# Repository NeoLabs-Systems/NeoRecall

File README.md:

<h1 align="center">NeoRecall</h1>

<p align="center"><strong>Private audio memory you host yourself.</strong></p>

Browser and coarse server analytics are enabled by default and can be disabled; see [analytics](docs/docs/analytics.md).

<p align="center">
  Records your day anywhere, turns every conversation into a searchable memory,<br>
  and answers from it. On your hardware, with the models you choose.
</p>

<p align="center">

</p>

<p align="center">

</p>

<p align="center">
  
</p>

https://github.com/user-attachments/assets/eb40bc78-905b-459a-bdea-a49aba3c9c09

<table>
  <tr>
    <td width="33%" valign="top">
      <h3>🏠 On your hardware</h3>
      Your server, your database, your search index.<br>
      Desktop app, Docker or one script.
    </td>
    <td width="33%" valign="top">
      <h3>🔐 Yours</h3>
      Open source under AGPL-3.0.<br>
      Any transcription and language model, local ones included.
    </td>
    <td width="33%" valign="top">
      <h3>🧾 Proof before delete</h3>
      Audio is removed only after the transcript is durable.
    </td>
  </tr>
</table>

---

## 🚀 Install

| | | |
| --- | --- | --- |
| 🖥️ **Desktop app** | macOS 13+ and Windows 10/11. **Set up NeoRecall on this computer** installs the server for you, no terminal. | [Download](https://github.com/NeoLabs-Systems/NeoRecall/releases/latest) |
| 🐳 **Docker** | Home servers, NAS boxes and VPS. | [Guide](docs/docs/installation.md#docker-compose) |
| 📜 **Script** | Linux or macOS with Git and Node.js 20+. | [Guide](docs/docs/installation.md) |

**Script**

```bash
bash <(curl -fsSL https://raw.githubusercontent.com/NeoLabs-Systems/NeoRecall/main/install.sh)
```

Then open **http://localhost:4500** once `neorecall status` reports a running service. The first account you create becomes the administrator; the app then asks for your transcription and language-model services (or an on-host model) and tests both.

## ✨ What it does

<table>
  <tr>
    <td width="33%" valign="top"><b>🎙️ Records anywhere</b><br>Browser, macOS and Windows with microphone and system audio. Quick capture sits in your tray.</td>
    <td width="33%" valign="top"><b>🧠 Memories, not transcripts</b><br>Each conversation becomes one memory with people, promises, decisions and tasks, written when it ends.</td>
    <td width="33%" valign="top"><b>💬 Ask your day</b><br>"What did I agree to this morning?" Answers cite the moments they came from.</td>
  </tr>
  <tr>
    <td valign="top"><b>🗣️ Knows who said what</b><br>Speech and voices are detected on your machine (31 MB of models). The same voice is recognized weeks later.</td>
    <td valign="top"><b>♾️ Never stops</b><br>Upload, transcription and conversation detection run during capture. Long recordings are read in windows and folded into one memory.</td>
    <td valign="top"><b>📴 Offline first</b><br>Clients buffer decodable chunks and resume idempotent uploads when the server is back.</td>
  </tr>
  <tr>
    <td valign="top"><b>📟 Wearables and devices</b><br>Omi, Plaud, Memoket and more over Bluetooth, plus NeoRecall Desk, a Raspberry Pi call recorder.</td>
    <td valign="top"><b>🎧 Meetings and voice</b><br>Zoom, Teams, Webex and FaceTime detection, and a Discord notetaker bot you run yourself.</td>
    <td valign="top"><b>🔌 NeoAgent and MCP</b><br>Connect <a href="https://github.com/NeoLabs-Systems/NeoAgent">NeoAgent</a>, or paste the MCP URL into Claude, ChatGPT or Cursor for read-only recall.</td>
  </tr>
  <tr>
    <td valign="top"><b>📝 Context</b><br>Add highlights, notes, photos and files while recording. They attach to the right memory.</td>
    <td valign="top"><b>🛡️ Consent built in</b><br>A recording notice and a persistent recording state. There is no covert mode.</td>
    <td valign="top"><b>👥 Multi-user</b><br>Per-account memory, admin role, two-factor and security keys, encrypted backups.</td>
  </tr>
</table>

**Inference:** bring any OpenAI-compatible transcription and language-model service, or run Whistle (speech to text) and Gemma 2 2B (memories and Ask) on the server itself. NeoRecall bundles no model you did not choose.

## 🧭 Explore it

| 🕒 Moments | 🧠 Memories |
| --- | --- |
|  |  |
| **💬 Ask** | **🔎 One memory** |
|  |  |

## 📚 Docs

| Start | Use | Run |
| --- | --- | --- |
| [Installation](docs/docs/installation.md) | [Recording](docs/docs/recording.md) | [Configuration](docs/docs/configuration.md) |
| [Privacy and consent](docs/docs/privacy-and-consent.md) | [NeoRecall Desk](docs/docs/desk-appliance.md) | [Troubleshooting](docs/docs/troubleshooting.md) |
| [Architecture](docs/docs/architecture.md) | [Contributing](CONTRIBUTING.md) | [Security](SECURITY.md) |

Full docs: **[neolabs-systems.github.io/NeoRecall/docs](https://neolabs-systems.github.io/NeoRecall/docs/)**

## 🧪 Project status

- **Beta.** Maintained mainly by one person. Expect breaking changes.
- **Privacy.** Read [privacy and consent](docs/docs/privacy-and-consent.md) and get the consent your jurisdiction requires before recording anyone else.
- **Help.** [Discussions](https://github.com/NeoLabs-Systems/NeoRecall/discussions) for questions, [Issues](https://github.com/NeoLabs-Systems/NeoRecall/issues) for bugs, [SECURITY.md](SECURITY.md) for vulnerabilities.

## 📄 License

[AGPL-3.0-only](LICENSE).

<p align="center"><sub>Made with ❤️ by <a href="https://github.com/neooriginal">Neo</a> · <a href="https://github.com/NeoLabs-Systems">NeoLabs Systems</a></sub></p>

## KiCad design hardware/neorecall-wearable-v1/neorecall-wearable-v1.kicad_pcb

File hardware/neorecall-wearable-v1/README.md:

# NeoRecall Wearable v1 hardware

This directory contains the concrete KiCad 10 schematic, PCB layout, and reviewed component set for a 28 mm × 38 mm NeoRecall recorder. It is a four-layer, 0.8 mm design with two TDK T5848 I²S microphones, Wi-Fi 6/BLE 5.3, removable 16 GB storage, protected three-wire LiPo support with a 10 kΩ pack thermistor, USB-C charging/flashing, and a center user/boot/wake button.

## What is complete

- Native KiCad schematic with exact part numbers, footprints, pin mapping, net names, and manufacturing notes.
- USB-C 5 V input, ESD protection, native ESP32-C6 USB, BQ24074 power-path charging, and a TPS63021 3.3 V buck-boost supply.
- Two independently selectable T5848 microphones on one stereo I²S bus at 1.85 V.
- SPI microSD with card detection, series damping, pull resistors, and local bulk capacitance.
- Visible recording and charging indicators, battery measurement, five zero-height UART/power/test pads, and monitored charger/regulator status.
- Manufacturer-drawing-derived footprints for the ESP32-C6-MINI-1, T5848, TPS63021 DSJ package, XFL4020 inductor, MEM2085 socket, and Molex USB-C socket.
- Machine-readable BOM, complete pin-to-net matrix, and electrical invariant checks.
- Four-layer fully connected PCB, locked symmetric ENIG stackup, all-layer antenna keepout, uninterrupted In1 GND plane, In2 3V3 distribution plane, and real KiCad 3D renders.
- Hardware power gates for both the microphone domain and microSD domain, with pull-downs that default both domains off during reset/deep sleep.
- Internal rear-side microSD socket whose complete body/card envelope stays inside the PCB outline.
- Hardware-bound recording indicator: powering the microphone domain necessarily lights the red LED.

The board is a **Rev C production candidate**, not production-qualified hardware. ERC, schematic parity, opens, shorts, ordinary copper clearance, and track-crossing checks are zero. The remaining nine DRC markers are the exact reviewed acoustic-port and connector-edge constructions in `DRC_WAIVERS.md`. The BQ_TS escape was narrowed locally to 0.10 mm and now retains at least 0.20 mm routed-edge clearance for JLCPCB. The package is for EVT/DFM, not unattended volume release.

## Files

- `neorecall-wearable-v1.kicad_sch` — generated KiCad schematic.
- `neorecall-wearable-v1.kicad_pro` — KiCad project.
- `neorecall-wearable-v1.kicad_pcb` — actual four-layer PCB layout.
- `renders/neorecall-top.png`, `renders/neorecall-bottom.png`, and `renders/neorecall-usb.png` — KiCad board and connector renders.
- `../../output/pdf/neorecall-wearable-v1-schematic.pdf` — rendered one-page A2 schematic PDF.
- `bom.csv` — one row per populated component with manufacturer part numbers.
- `pin-net-matrix.csv` — auditable pin-level connectivity.
- `design-summary.json` — dimensions and power/storage configuration.
- `PLACEMENT.md` — concrete PCB placement and thickness plan.
- `ASSEMBLY.md` — hand-assembly, bring-up, and battery-safety procedure.
- `SOURCES.md` — primary manufacturer sources used for electrical and mechanical decisions.
- `tools/generate_schematic.py` — electrical source of truth and deterministic generator.
- `tools/verify_design.py` — offline structural and electrical verification.
- `tools/verify_release.py` — verifies ERC/DRC reports and the exact mechanical-waiver signature.
- `tools/verify_functional_margins.py` — independently rechecks critical pin paths, charger/ADC/audio/storage arithmetic, and the complete JLC ZIP without importing the generator.
- `tools/verify_layout.py` — verifies board geometry, planes, antenna keepout, internal card envelope, switch nodes, power widths, and USB routing metrics with pcbnew.
- `tools/export_jlcpcb.sh` — generates the conventional four-layer Gerber/drill ZIP for direct JLCPCB upload.
- `firmware/manufacturing-test/` — build-tested ESP-IDF first-article firmware for power status, battery ADC, stereo microphones, microSD write/read/isolation, button, and deep-sleep wake.
- `fabrication/` — current EVT Gerber/drill/placement package and fab notes.
- `ELECTRICAL_AUDIT.md` — calculations, fault scenarios, sourcing review, and physical qualification matrix.

## Generate and verify

The only Python dependency is small; no KiCad application or model download is needed to regenerate the schematic.

```bash
python3 -m venv .venv-hardware
.venv-hardware/bin/pip install -r hardware/neorecall-wearable-v1/tools/requirements.txt
.venv-hardware/bin/python hardware/neorecall-wearable-v1/tools/generate_schematic.py
# Run sync_board.py with KiCad 10's bundled Python/pcbnew after regenerating.
.venv-hardware/bin/python hardware/neorecall-wearable-v1/tools/verify_design.py
.venv-hardware/bin/python hardware/neorecall-wearable-v1/tools/verify_release.py
.venv-hardware/bin/python hardware/neorecall-wearable-v1/tools/verify_functional_margins.py
# Run verify_layout.py with KiCad's bundled Python/pcbnew environment.
```

Open `hardware/neorecall-wearable-v1/neorecall-wearable-v1.kicad_pro` in KiCad 10 or newer. Run ERC and DRC again after any hand edit. Before ordering a PCB, select the actual 0.8 mm board-house stackup, solve USB D+/D− for 90 Ω differential impedance, and compare 1:1 footprint prints against physical parts.

The assembly BOM is now 71 fitted parts. TP1–TP5 are bare ENIG pogo/solder pads, excluded from the BOM and pick-and-place data: GPIO16/UART TX, GPIO17/UART RX, ESP_EN, 3V3, and GND. GPIO16/17 can be reassigned by firmware after boot, providing a compact two-signal expansion/debug interface without a connector, board-area increase, or assembly height.

## Fixed electrical decisions

- MCU/radio: `ESP32-C6-MINI-1-H8`, integrated antenna and 8 MB flash.
- Storage: `MEM2085-00-115-00-A` low-profile microSD socket with a genuine 16 GB high-endurance card.
- Microphones: two `MMICT5848-00-012`, one LR pin low and one high.
- Charger: `BQ24074RGTR`, approximately 201 mA cell charge, 500 mA USB input mode, power-path enabled.
- Main supply: fixed 3.3 V `TPS63021DSJR` with `XFL4020-152MEC` and 66 µF nominal output capacitance.
- Microphone supply: switchable 1.85 V `TPS7A20185PDBVR` plus `TXU0304PWR` level translation.
- Storage supply: switchable 3.3 V `TPS22918DBVR` with a 1 nF CT capacitor for an approximately 1.68 ms rail rise; firmware must unmount the card, disable SPI pins, then drive `SD_POWER_EN` low before deep sleep.
- Battery: protected 1S LiPo only, keyed three-pole JST-SH: pin 1 BAT+, pin 2 pack 10 kΩ NTC to GND at 25 °C, pin 3 GND.

The pack thermistor gives the BQ24074 real charge-temperature qualification. It is not a substitute for a protected, reputable cell, a locked mating-cable pinout, or enclosure thermal validation.

## Deep-sleep design

- `MIC_POWER_EN` removes the microphone LDO/translator domain; `R31` keeps it off through reset.
- `SD_POWER_EN` removes microSD and all card pull-up current; `R32` keeps it off through reset.
- TPS63021 power-save mode remains enabled so the always-on 3.3 V rail is efficient at light load.
- The battery divider is 1 MΩ + 330 kΩ, approximately 3.2 µA at a full 4.2 V cell.
- The center button reaches both GPIO0 (deep-sleep-capable wake) and GPIO9 (ROM boot strap); firmware must configure both as inputs and use GPIO0 for deep-sleep wake. There is intentionally no covert always-recording mode.

The estimated board-level deep-sleep budget is a design estimate, not a guaranteed measurement. Regulator, charger, MCU, divider, load-switch, translator, card leakage, temperature, and assembly contamination must be measured on at least three assembled boards before an endurance claim is published.

## Size and sourcing decision

The active outline remains 28 mm × 38 mm. The RF module antenna keepout, internal microSD envelope, opposed microphone ports, and edge-mounted USB and battery connectors set the usable geometry; shrinking the center PTS810 switch does not reduce the outline. Replacing it with a less common, less hand-reworkable switch would trade usability and sourcing resilience for no board-size win. The retained active ICs are current manufacturer parts, while the five incorrectly BOM-listed test-point components have been removed. The 1.85 V microphone rail and level translator remain electrically necessary because T5848 operates from 1.62–1.98 V; the obsolete 3.3 V ICS-43434 is not a valid consolidation substitute.

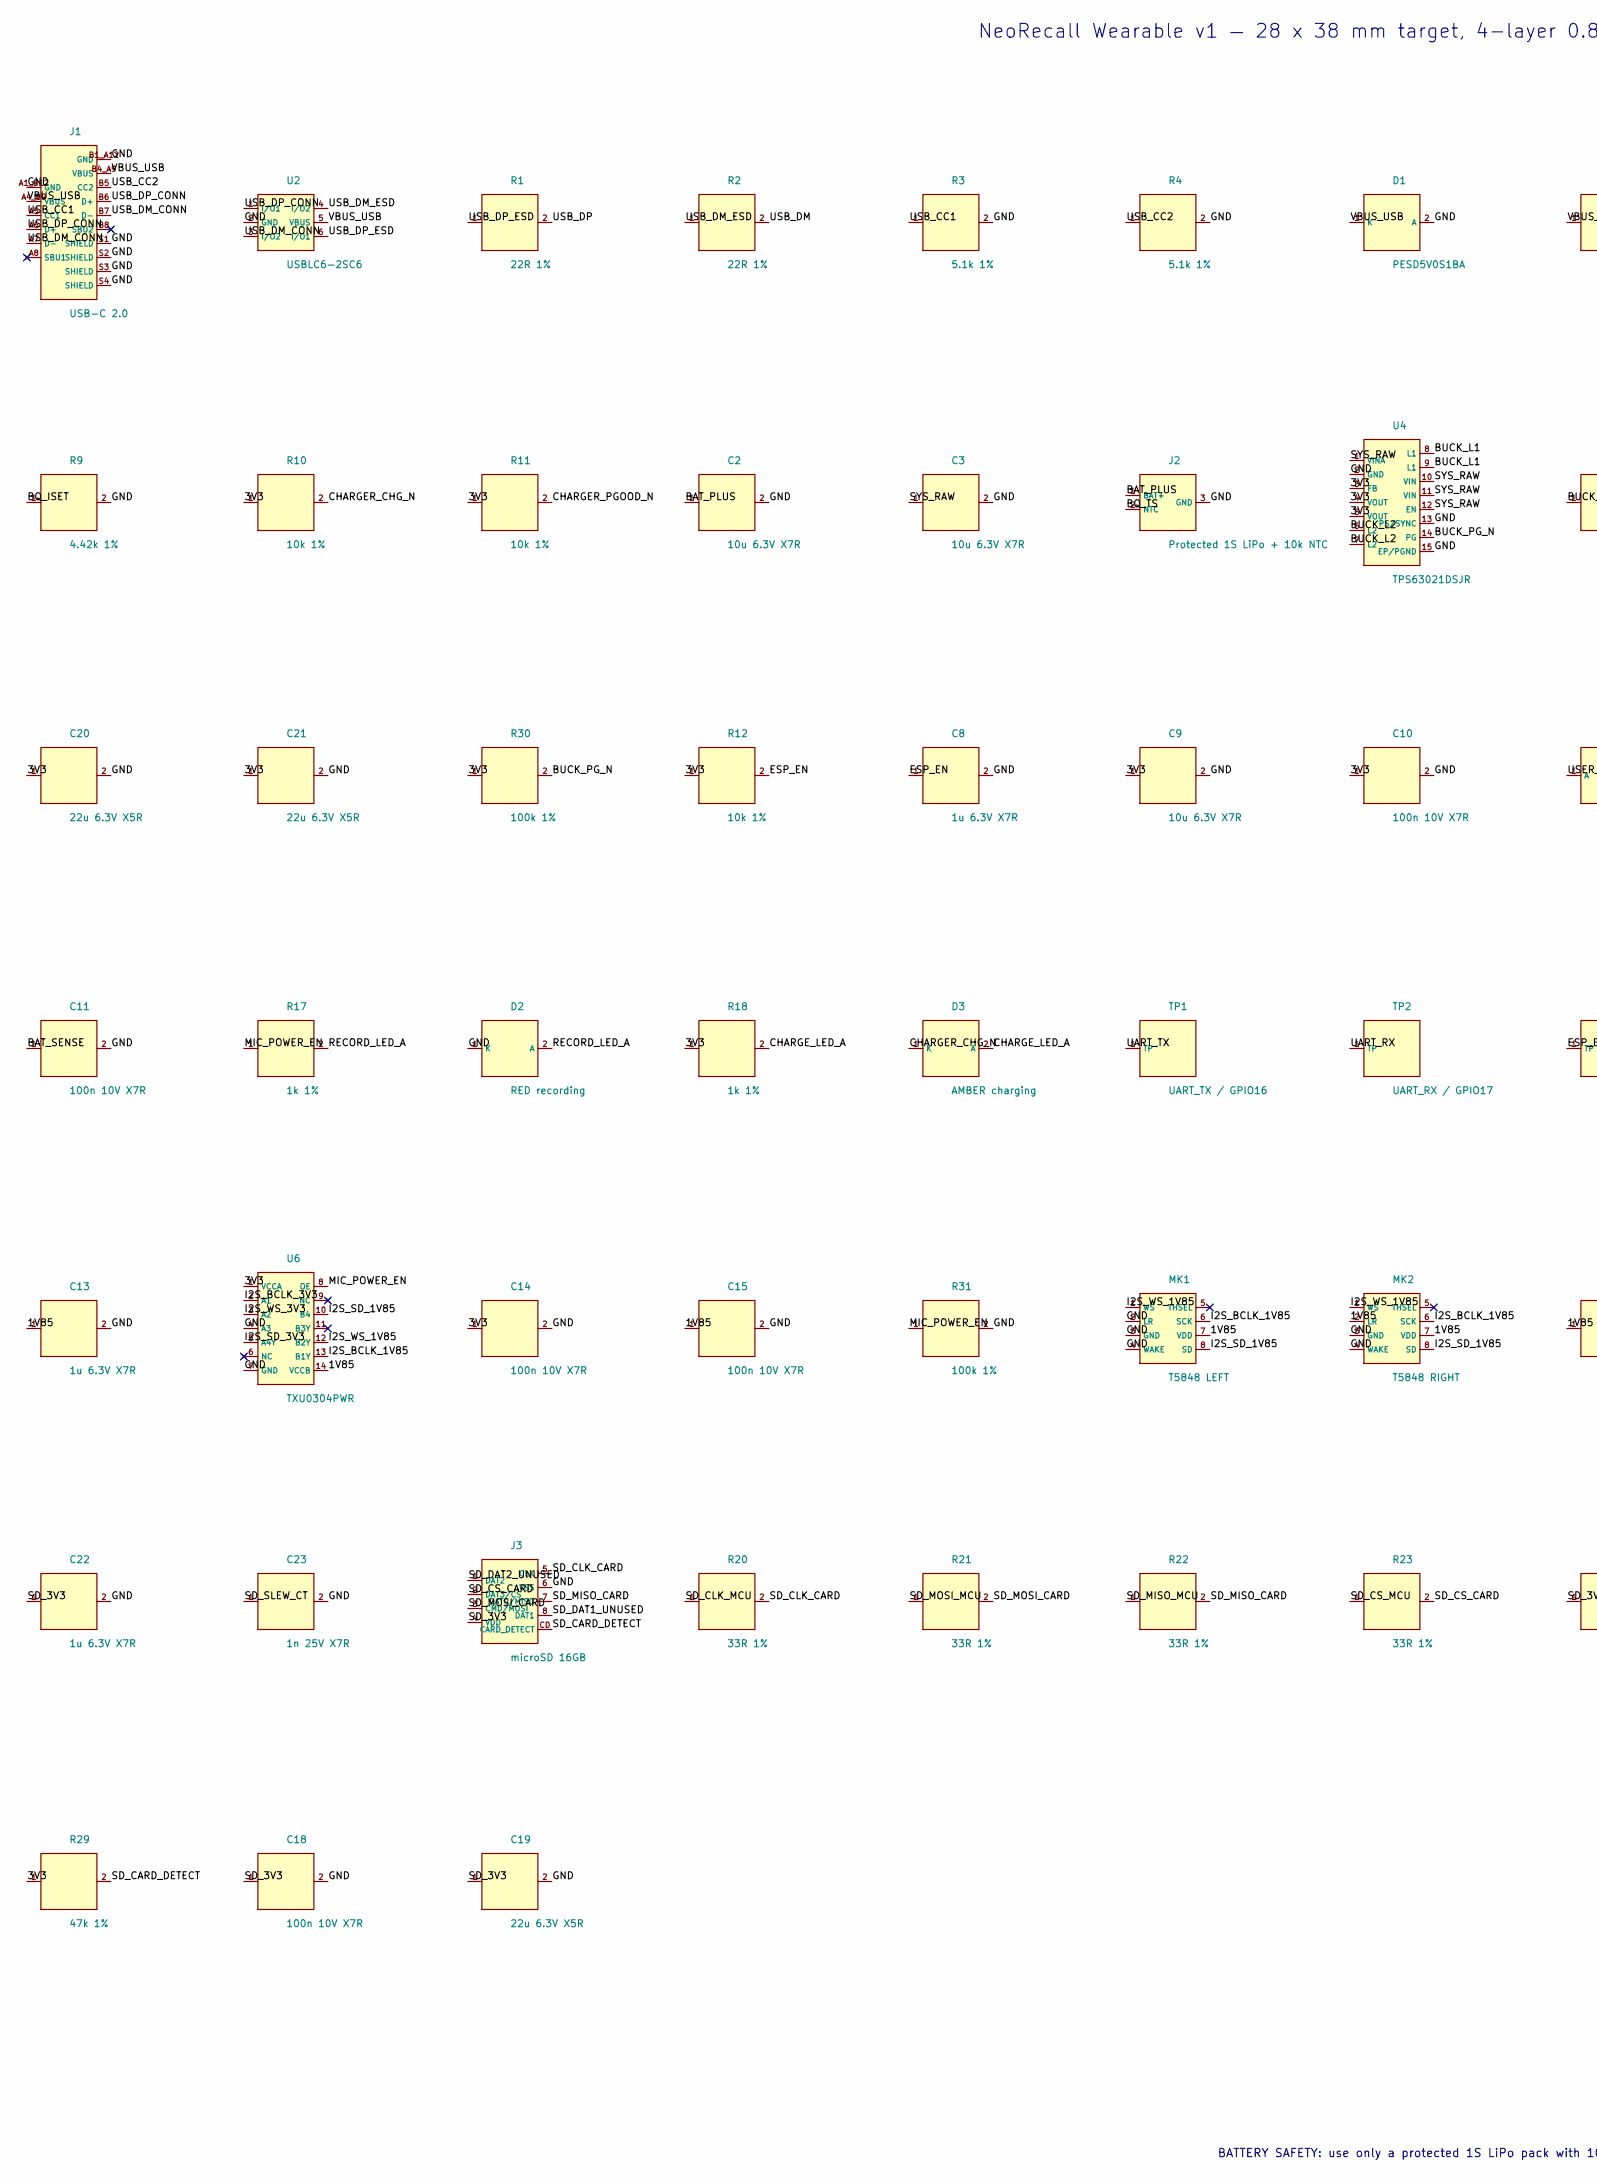
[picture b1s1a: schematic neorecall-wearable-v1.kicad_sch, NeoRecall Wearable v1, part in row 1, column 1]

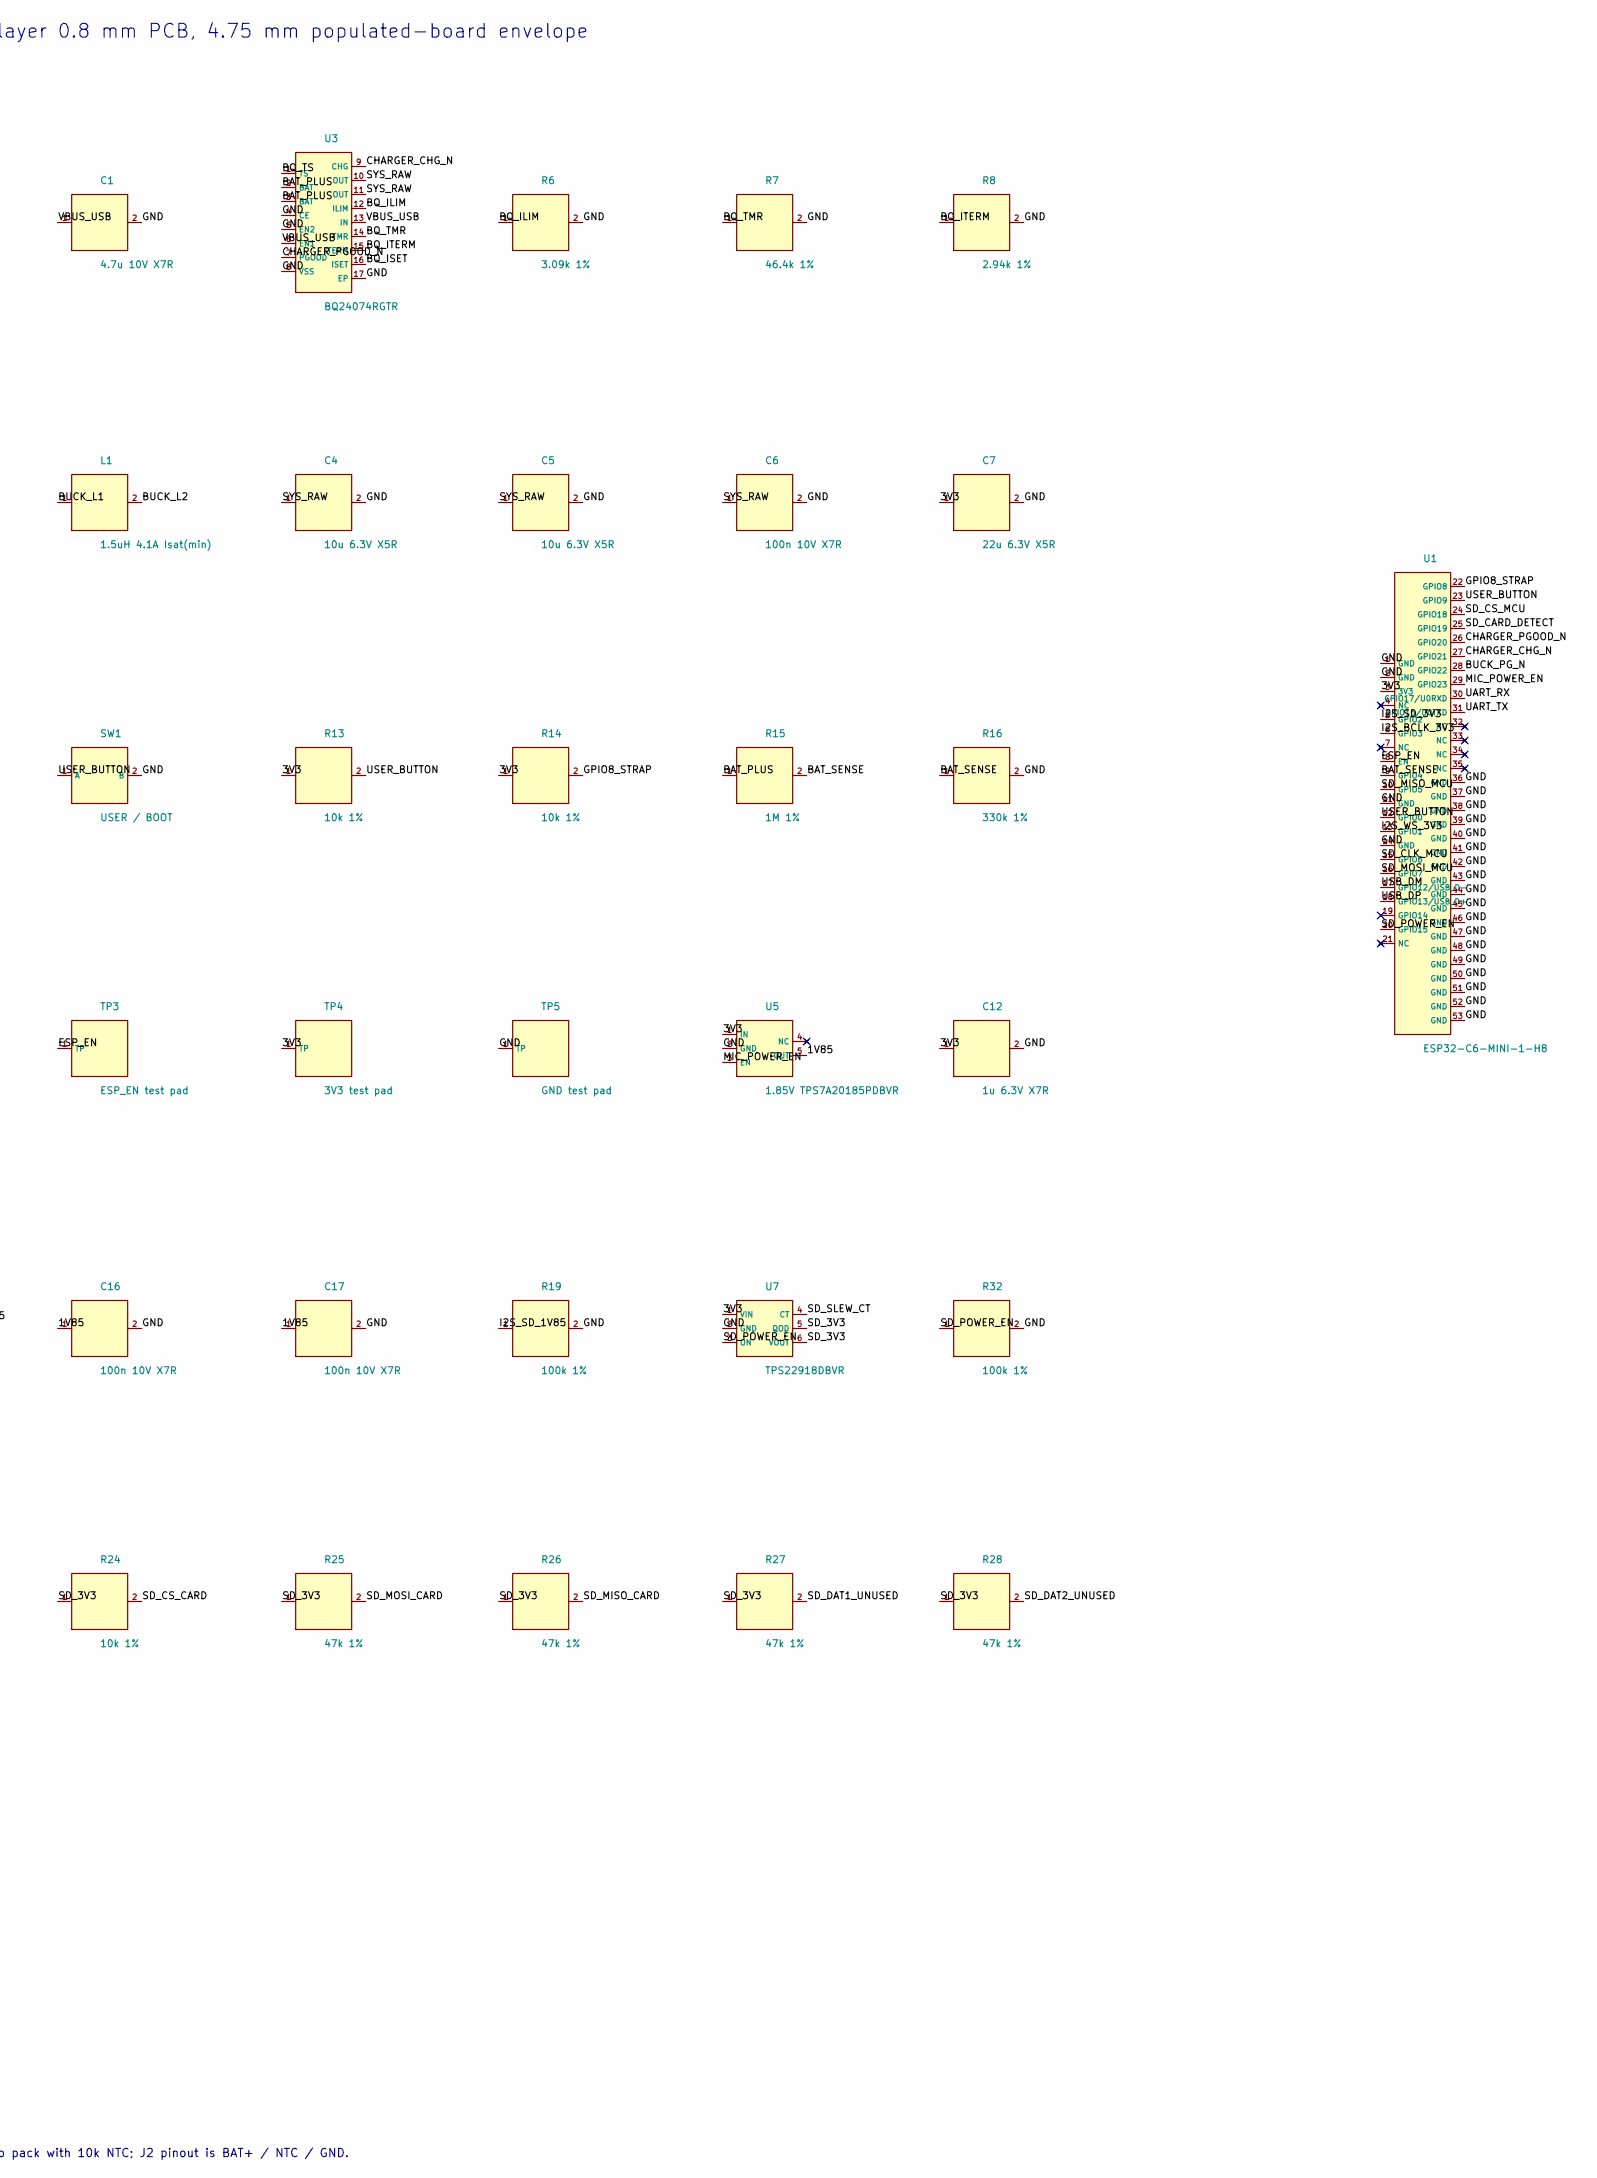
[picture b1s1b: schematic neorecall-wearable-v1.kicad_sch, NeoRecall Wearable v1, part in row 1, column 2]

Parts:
C1: 4.7u 10V X7R; C_0603_1608Metric
C2, C3, C9: 10u 6.3V X7R; C_0603_1608Metric
C4, C5: 10u 6.3V X5R; C_0603_1608Metric
C6, C10, C11, C14, C15, C16, C17, C18: 100n 10V X7R; C_0603_1608Metric
C7, C19, C20, C21: 22u 6.3V X5R; C_0805_2012Metric
C8, C12, C13, C22: 1u 6.3V X7R; C_0603_1608Metric
C23: 1n 25V X7R; C_0402_1005Metric
D1: PESD5V0S1BA; D_SOD-323
D2: RED recording; LED_0603_1608Metric
D3: AMBER charging; LED_0603_1608Metric
J1: USB-C 2.0; Molex_2169900003
J2: Protected 1S LiPo + 10k NTC; JST_SH_SM03B-SRSS-TB_1x03-1MP_P1.00mm_Horizontal
J3: microSD 16GB; GCT_MEM2085
L1: 1.5uH 4.1A Isat(min); Coilcraft_XFL4020
MK1: T5848 LEFT; T5848_LGA8_BottomPort
MK2: T5848 RIGHT; T5848_LGA8_BottomPort
R1, R2: 22R 1%; R_0402_1005Metric
R3, R4: 5.1k 1%; R_0603_1608Metric
R6: 3.09k 1%; R_0603_1608Metric
R7: 46.4k 1%; R_0603_1608Metric
R8: 2.94k 1%; R_0603_1608Metric
R9: 4.42k 1%; R_0603_1608Metric
R10, R11, R12, R13, R14, R24: 10k 1%; R_0603_1608Metric
R15: 1M 1%; R_0603_1608Metric
R16: 330k 1%; R_0603_1608Metric
R17, R18: 1k 1%; R_0603_1608Metric
R19, R30, R31, R32: 100k 1%; R_0603_1608Metric
R20, R21, R22, R23: 33R 1%; R_0603_1608Metric
R25, R26, R27, R29: 47k 1%; R_0603_1608Metric
R28: 47k 1%; R_0402_1005Metric
SW1: USER / BOOT; SW_SPST_PTS810
TP1: UART_TX / GPIO16; TestPoint_Pad_D1.0mm
TP2: UART_RX / GPIO17; TestPoint_Pad_D1.0mm
TP3: ESP_EN test pad; TestPoint_Pad_D1.0mm
TP4: 3V3 test pad; TestPoint_Pad_D1.0mm
TP5: GND test pad; TestPoint_Pad_D1.0mm
U1: ESP32-C6-MINI-1-H8; ESP32-C6-MINI-1
U2: USBLC6-2SC6; SOT-23-6
U3: BQ24074RGTR; VQFN-16-1EP_3x3mm_P0.5mm_EP1.45x1.45mm
U4: TPS63021DSJR; TI_DSJ_VSON14_3x4mm
U5: 1.85V TPS7A20185PDBVR; SOT-23-5
U6: TXU0304PWR; TSSOP-14_4.4x5mm_P0.65mm
U7: TPS22918DBVR; SOT-23-6

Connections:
/1V85: C13.1, C15.1, C16.1, C17.1, MK1.7 (VDD), MK2.2 (LR), MK2.7 (VDD), U5.5 (OUT), U6.14 (VCCB)
/3V3: C7.1, C9.1, C10.1, C12.1, C14.1, C20.1, C21.1, R10.1, R11.1, R12.1, R13.1, R14.1, R18.1, R29.1, R30.1, TP4.1, U1.3 (3V3), U4.3 (FB), U4.4 (VOUT), U4.5 (VOUT), U5.1 (IN), U6.1 (VCCA), U7.1 (VIN)
/BAT_PLUS: C2.1, J2.1 (BAT+), R15.1, U3.2 (BAT), U3.3 (BAT)
/BAT_SENSE: C11.1, R15.2, R16.1, U1.9 (GPIO4)
/BQ_ILIM: R6.1, U3.12 (ILIM)
/BQ_ISET: R9.1, U3.16 (ISET)
/BQ_ITERM: R8.1, U3.15 (ITERM)
/BQ_TMR: R7.1, U3.14 (TMR)
/BQ_TS: J2.2 (NTC), U3.1 (TS)
/BUCK_L1: L1.1, U4.8 (L1), U4.9 (L1)
/BUCK_L2: L1.2, U4.6 (L2), U4.7 (L2)
/BUCK_PG_N: R30.2, U1.28 (GPIO22), U4.14 (PG)
/CHARGER_CHG_N: D3.1 (K), R10.2, U1.27 (GPIO21), U3.9 (CHG)
/CHARGER_PGOOD_N: R11.2, U1.26 (GPIO20), U3.7 (PGOOD)
/CHARGE_LED_A: D3.2 (A), R18.2
/ESP_EN: C8.1, R12.2, TP3.1, U1.8 (EN)
/GND: C1.2, C2.2, C3.2, C4.2, C5.2, C6.2, C7.2, C8.2, C9.2, C10.2, C11.2, C12.2, C13.2, C14.2, C15.2, C16.2, C17.2, C18.2, C19.2, C20.2, C21.2, C22.2, C23.2, D1.2 (A), D2.1 (K), J1.A1_B12 (GND), J1.B1_A12 (GND), J1.S1 (SHIELD), J1.S2 (SHIELD), J1.S3 (SHIELD), J1.S4 (SHIELD), J2.3 (GND), J3.6 (VSS), MK1.2 (LR), MK1.3 (GND), MK1.4 (WAKE), MK2.3 (GND), MK2.4 (WAKE), R3.2, R4.2, R6.2, R7.2, R8.2, R9.2, R16.2, R19.2, R31.2, R32.2, SW1.2 (B), TP5.1, U1.1 (GND), U1.2 (GND), U1.11 (GND), U1.14 (GND), U1.36 (GND), U1.37 (GND), U1.38 (GND), U1.39 (GND), U1.40 (GND), U1.41 (GND), U1.42 (GND), U1.43 (GND), U1.44 (GND), U1.45 (GND), U1.46 (GND), U1.47 (GND), U1.48 (GND), U1.49 (GND), U1.50 (GND), U1.51 (GND), U1.52 (GND), U1.53 (GND), U2.2 (GND), U3.4 (CE), U3.5 (EN2), U3.8 (VSS), U3.17 (EP), U4.2 (GND), U4.13 (PS/SYNC), U4.15 (EP/PGND), U5.2 (GND), U6.4 (A3), U6.7 (GND), U7.2 (GND)
/GPIO8_STRAP: R14.2, U1.22 (GPIO8)
/I2S_BCLK_1V85: MK1.6 (SCK), MK2.6 (SCK), U6.13 (B1Y)
/I2S_BCLK_3V3: U1.6 (GPIO3), U6.2 (A1)
/I2S_SD_1V85: MK1.8 (SD), MK2.8 (SD), R19.1, U6.10 (B4)
/I2S_SD_3V3: U1.5 (GPIO2), U6.5 (A4Y)
/I2S_WS_1V85: MK1.1 (WS), MK2.1 (WS), U6.12 (B2Y)
/I2S_WS_3V3: U1.13 (GPIO1), U6.3 (A2)
/MIC_POWER_EN: R17.1, R31.1, U1.29 (GPIO23), U5.3 (EN), U6.8 (OE)
/RECORD_LED_A: D2.2 (A), R17.2
/SD_3V3: C18.1, C19.1, C22.1, J3.4 (VDD), R24.1, R25.1, R26.1, R27.1, R28.1, U7.5 (QOD), U7.6 (VOUT)
/SD_CARD_DETECT: J3.CD (CARD_DETECT), R29.2, U1.25 (GPIO19)
/SD_CLK_CARD: J3.5 (CLK), R20.2
/SD_CLK_MCU: R20.1, U1.15 (GPIO6)
/SD_CS_CARD: J3.2 (DAT3/CS), R23.2, R24.2
/SD_CS_MCU: R23.1, U1.24 (GPIO18)
/SD_DAT1_UNUSED: J3.8 (DAT1), R27.2
/SD_DAT2_UNUSED: J3.1 (DAT2), R28.2
/SD_MISO_CARD: J3.7 (DAT0/MISO), R22.2, R26.2
/SD_MISO_MCU: R22.1, U1.10 (GPIO5)
/SD_MOSI_CARD: J3.3 (CMD/MOSI), R21.2, R25.2
/SD_MOSI_MCU: R21.1, U1.16 (GPIO7)
/SD_POWER_EN: R32.1, U1.20 (GPIO15), U7.3 (ON)
/SD_SLEW_CT: C23.1, U7.4 (CT)
/SYS_RAW: C3.1, C4.1, C5.1, C6.1, U3.10 (OUT), U3.11 (OUT), U4.1 (VINA), U4.10 (VIN), U4.11 (VIN), U4.12 (EN)
/UART_RX: TP2.1, U1.30 (GPIO17/U0RXD)
/UART_TX: TP1.1, U1.31 (GPIO16/U0TXD)
/USB_CC1: J1.A5 (CC1), R3.1
/USB_CC2: J1.B5 (CC2), R4.1
/USB_DM: R2.2, U1.17 (GPIO12/USB_D-)
/USB_DM_CONN: J1.A7 (D-), J1.B7 (D-), U2.3 (I/O2)
/USB_DM_ESD: R2.1, U2.4 (I/O2)
/USB_DP: R1.2, U1.18 (GPIO13/USB_D+)
/USB_DP_CONN: J1.A6 (D+), J1.B6 (D+), U2.1 (I/O1)
/USB_DP_ESD: R1.1, U2.6 (I/O1)
/USER_BUTTON: R13.2, SW1.1 (A), U1.12 (GPIO0), U1.23 (GPIO9)
/VBUS_USB: C1.1, D1.1 (K), J1.A4_B9 (VBUS), J1.B4_A9 (VBUS), U2.5 (VBUS), U3.6 (EN1), U3.13 (IN)

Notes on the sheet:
NeoRecall Wearable v1 — 28 x 38 mm target, 4-layer 0.8 mm PCB, 4.75 mm populated-board envelope
BATTERY SAFETY: use only a protected 1S LiPo pack with 10k NTC; J2 pinout is BAT+ / NTC / GND.

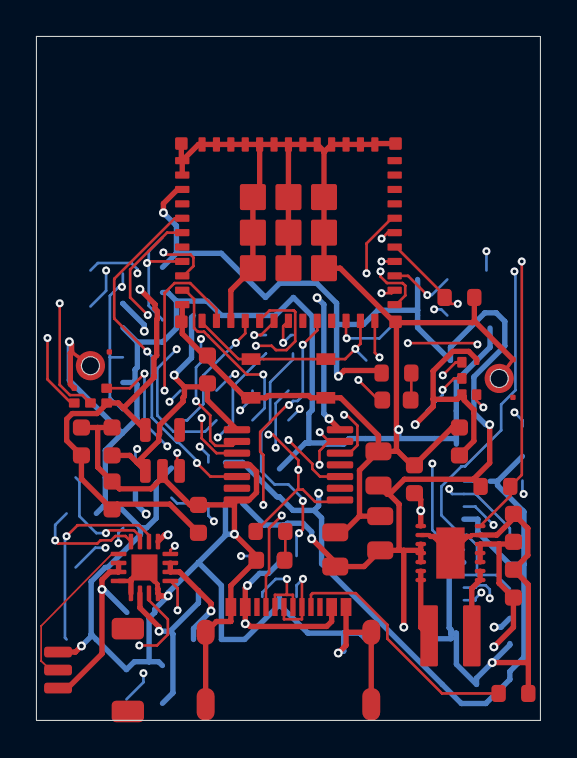
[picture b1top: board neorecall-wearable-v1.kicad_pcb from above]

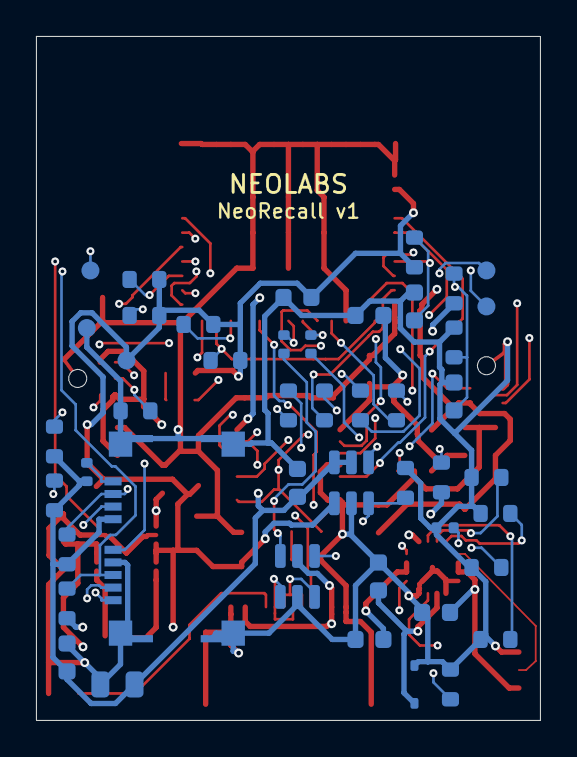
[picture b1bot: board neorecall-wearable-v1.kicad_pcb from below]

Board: 4 copper layers, 28.0 x 38.0 mm, 76 parts (46 on the bottom side), 53 nets.

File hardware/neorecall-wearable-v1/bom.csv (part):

Reference,Quantity,Value,Manufacturer,MPN,Footprint,Datasheet,Assembly note
J1,1,USB-C 2.0,Molex,216990-0003,NeoRecall_Wearable:Molex_2169900003,https://www.molex.com/en-us/products/part-detail/2169900003,Mid-mount; intended for 0.8 mm PCB
U2,1,USBLC6-2SC6,STMicroelectronics,USBLC6-2SC6,Package_TO_SOT_SMD:SOT-23-6,https://www.st.com/resource/en/datasheet/usblc6-2.pdf,
R1,1,22R 1%,Yageo,RC0402FR-0722RL,Resistor_SMD:R_0402_1005Metric,https://www.yageo.com/en/ProductSearch/PartDetail?partNo=RC0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,Place immediately at the ESP32 USB D+ pin; 0402 permits matched side-by-side breakout
R2,1,22R 1%,Yageo,RC0402FR-0722RL,Resistor_SMD:R_0402_1005Metric,https://www.yageo.com/en/ProductSearch/PartDetail?partNo=RC0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,Place immediately at the ESP32 USB D- pin; 0402 permits matched side-by-side breakout
R3,1,5.1k 1%,Yageo,RC0603FR-075K1L,Resistor_SMD:R_0603_1608Metric,https://www.yageo.com/,
R4,1,5.1k 1%,Yageo,RC0603FR-075K1L,Resistor_SMD:R_0603_1608Metric,https://www.yageo.com/,
D1,1,PESD5V0S1BA,Nexperia,"PESD5V0S1BA,115",Diode_SMD:D_SOD-323,https://assets.nexperia.com/documents/data-sheet/PESD5V0S1BA.pdf,
C1,1,4.7u 10V X7R,Murata,GRM188Z71A475KE15D,Capacitor_SMD:C_0603_1608Metric,https://www.murata.com/en-us/products/productdetail?partno=G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,
U3,1,BQ24074RGTR,Texas Instruments,BQ24074RGTR,Package_DFN_QFN:VQFN-16-1EP_3x3mm_P0.5mm_EP1.45x1.45mm,https://www.ti.com/lit/ds/symlink/bq24074.pdf,"201 mA charge, 20 mA termination, USB500 input mode"
R6,1,3.09k 1%,Yageo,RC0603FR-073K09L,Resistor_SMD:R_0603_1608Metric,https://www.yageo.com/,
R7,1,46.4k 1%,Yageo,RC0603FR-0746K4L,Resistor_SMD:R_0603_1608Metric,https://www.yageo.com/,
R8,1,2.94k 1%,Yageo,RC0603FR-072K94L,Resistor_SMD:R_0603_1608Metric,https://www.yageo.com/,
R9,1,4.42k 1%,Yageo,RC0603FR-074K42L,Resistor_SMD:R_0603_1608Metric,https://www.yageo.com/,
R10,1,10k 1%,Yageo,RC0603FR-0710KL,Resistor_SMD:R_0603_1608Metric,https://www.yageo.com/,
R11,1,10k 1%,Yageo,RC0603FR-0710KL,Resistor_SMD:R_0603_1608Metric,https://www.yageo.com/,
C2,1,10u 6.3V X7R,Murata,GRM188R60J106ME47D,Capacitor_SMD:C_0603_1608Metric,https://www.murata.com/,
C3,1,10u 6.3V X7R,Murata,GRM188R60J106ME47D,Capacitor_SMD:C_0603_1608Metric,https://www.murata.com/,
J2,1,Protected 1S LiPo + 10k NTC,JST,SM03B-SRSS-TB(LF)(SN),Connector_JST:JST_SH_SM03B-SRSS-TB_1x03-1MP_P1.00mm_Horizontal,https://www.jst-mfg.com/product/index.php?series=231,"Mating pack must be protected and use pin 1 BAT+, pin 2 10k NTC to GND at 25 C, pin 3 GND"
U4,1,TPS63021DSJR,Texas Instruments,TPS63021DSJR,NeoRecall_Wearable:TI_DSJ_VSON14_3x4mm,https://www.ti.com/lit/ds/symlink/tps63021.pdf,Fixed 3.3 V; power-save enabled; sized for Wi-Fi and microSD transient load
L1,1,1.5uH 4.1A Isat(min),Coilcraft,XFL4020-152MEC,NeoRecall_Wearable:Coilcraft_XFL4020,https://www.coilcraft.com/en-us/products/power/shielded-indu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,
C4,1,10u 6.3V X5R,Murata,GRM188R60J106ME47D,Capacitor_SMD:C_0603_1608Metric,https://www.murata.com/,
C5,1,10u 6.3V X5R,Murata,GRM188R60J106ME47D,Capacitor_SMD:C_0603_1608Metric,https://www.murata.com/,
C6,1,100n 10V X7R,Murata,GRM188R71A104KA01D,Capacitor_SMD:C_0603_1608Metric,https://www.murata.com/,
C7,1,22u 6.3V X5R,Murata,GRM21BR60J226ME39L,Capacitor_SMD:C_0805_2012Metric,https://www.murata.com/,
C20,1,22u 6.3V X5R,Murata,GRM21BR60J226ME39L,Capacitor_SMD:C_0805_2012Metric,https://www.murata.com/,
C21,1,22u 6.3V X5R,Murata,GRM21BR60J226ME39L,Capacitor_SMD:C_0805_2012Metric,https://www.murata.com/,
R30,1,100k 1%,Yageo,RC0603FR-07100KL,Resistor_SMD:R_0603_1608Metric,https://www.yageo.com/,
U1,1,ESP32-C6-MINI-1-H8,Espressif Systems,ESP32-C6-MINI-1-H8,NeoRecall_Wearable:ESP32-C6-MINI-1,https://documentation.espressif.com/esp32-c6-mini-1_mini-1u_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,Integrated PCB antenna; antenna end must be at board edge with full all-layer keepout
R12,1,10k 1%,Yageo,RC0603FR-0710KL,Resistor_SMD:R_0603_1608Metric,https://www.yageo.com/,
C8,1,1u 6.3V X7R,Murata,GRM188R60J105KA01D,Capacitor_SMD:C_0603_1608Metric,https://www.murata.com/,
C9,1,10u 6.3V X7R,Murata,GRM188R60J106ME47D,Capacitor_SMD:C_0603_1608Metric,https://www.murata.com/,
C10,1,100n 10V X7R,Murata,GRM188R71A104KA01D,Capacitor_SMD:C_0603_1608Metric,https://www.murata.com/,
SW1,1,USER / BOOT,C&K,PTS810SJM250SMTRLFS,Button_Switch_SMD:SW_SPST_PTS810,https://www.ckswitches.com/media/1476/pts810.pdf,"Place at exact PCB center (14.0 mm, 19.0 mm)"
R13,1,10k 1%,Yageo,RC0603FR-0710KL,Resistor_SMD:R_0603_1608Metric,https://www.yageo.com/,
R14,1,10k 1%,Yageo,RC0603FR-0710KL,Resistor_SMD:R_0603_1608Metric,https://www.yageo.com/,
R15,1,1M 1%,Yageo,RC0603FR-071ML,Resistor_SMD:R_0603_1608Metric,https://www.yageo.com/,
R16,1,330k 1%,Yageo,RC0603FR-07330KL,Resistor_SMD:R_0603_1608Metric,https://www.yageo.com/,
C11,1,100n 10V X7R,Murata,GRM188R71A104KA01D,Capacitor_SMD:C_0603_1608Metric,https://www.murata.com/,
R17,1,1k 1%,Yageo,RC0603FR-071KL,Resistor_SMD:R_0603_1608Metric,https://www.yageo.com/,Hardware-binds the red indicator to microphone-domain power; firmware cannot power the microphones with the indicator off
D2,1,RED recording,Wurth Elektronik,150060RS75000,LED_SMD:LED_0603_1608Metric,https://www.we-online.com/components/products/datasheet/1500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,Must be visibly on whenever audio capture is active; no covert mode
R18,1,1k 1%,Yageo,RC0603FR-071KL,Resistor_SMD:R_0603_1608Metric,https://www.yageo.com/,
D3,1,AMBER charging,Wurth Elektronik,150060YS75000,LED_SMD:LED_0603_1608Metric,https://www.we-online.com/components/products/datasheet/1500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,
U5,1,1.85V TPS7A20185PDBVR,Texas Instruments,TPS7A20185PDBVR,Package_TO_SOT_SMD:SOT-23-5,https://www.ti.com/lit/ds/symlink/tps7a20.pdf,
C12,1,1u 6.3V X7R,Murata,GRM188R60J105KA01D,Capacitor_SMD:C_0603_1608Metric,https://www.murata.com/,
C13,1,1u 6.3V X7R,Murata,GRM188R60J105KA01D,Capacitor_SMD:C_0603_1608Metric,https://www.murata.com/,
U6,1,TXU0304PWR,Texas Instruments,TXU0304PWR,Package_SO:TSSOP-14_4.4x5mm_P0.65mm,https://www.ti.com/lit/ds/symlink/txu0304.pdf,A1/A2 translate clocks 3.3V to 1.85V; B4/A4Y translate microphone data to 3.3V
C14,1,100n 10V X7R,Murata,GRM188R71A104KA01D,Capacitor_SMD:C_0603_1608Metric,https://www.murata.com/,
C15,1,100n 10V X7R,Murata,GRM188R71A104KA01D,Capacitor_SMD:C_0603_1608Metric,https://www.murata.com/,
R31,1,100k 1%,Yageo,RC0603FR-07100KL,Resistor_SMD:R_0603_1608Metric,https://www.yageo.com/,Keeps microphone LDO and level translator disabled while the ESP32 GPIO is high impedance at reset
MK1,1,T5848 LEFT,TDK InvenSense,MMICT5848-00-012,NeoRecall_Wearable:T5848_LGA8_BottomPort,https://www.mouser.com/catalog/specsheets/TDK_7302024_DS_000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,Left I2S slot; bottom acoustic port uses a 1.0 mm non-plated PCB hole
MK2,1,T5848 RIGHT,TDK InvenSense,MMICT5848-00-012,NeoRecall_Wearable:T5848_LGA8_BottomPort,https://www.mouser.com/catalog/specsheets/TDK_7302024_DS_000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,Right I2S slot; bottom acoustic port uses a 1.0 mm non-plated PCB hole
C16,1,100n 10V X7R,Murata,GRM188R71A104KA01D,Capacitor_SMD:C_0603_1608Metric,https://www.murata.com/,
C17,1,100n 10V X7R,Murata,GRM188R71A104KA01D,Capacitor_SMD:C_0603_1608Metric,https://www.murata.com/,
R19,1,100k 1%,Yageo,RC0603FR-07100KL,Resistor_SMD:R_0603_1608Metric,https://www.yageo.com/,
U7,1,TPS22918DBVR,Texas Instruments,TPS22918DBVR,Package_TO_SOT_SMD:SOT-23-6,https://www.ti.com/lit/ds/symlink/tps22918.pdf,Low-leakage microSD power gate; controlled rise time limits card-rail inrush and QOD discharges the rail when disabled
R32,1,100k 1%,Yageo,RC0603FR-07100KL,Resistor_SMD:R_0603_1608Metric,https://www.yageo.com/,Keeps microSD power disabled during reset and deep sleep
C22,1,1u 6.3V X7R,Murata,GRM188R60J105KA01D,Capacitor_SMD:C_0603_1608Metric,https://www.murata.com/,
C23,1,1n 25V X7R,Murata,GRM155R71E102KA01D,Capacitor_SMD:C_0402_1005Metric,https://www.murata.com/en-us/products/productdetail?partno=G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,Programs an approximately 1.68 ms 3.3 V load-switch rise time to limit microSD capacitor inrush
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

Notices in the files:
README.md:
AGPL-3.0 license
